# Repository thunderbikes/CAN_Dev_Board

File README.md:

# Alex CANBus DevBoard

## Repo:

https://github.com/alexm35644/CANBus_Devkit

## PCB:

[https://kicanvas.org/?github=https%3A%2F%2Fgithub.com%2Falexm35644%2FCANBus_Devkit%2Fblob%2Fmain%2FKiCAD_MCPtest%2FKiCAD_MCPtest.kicad_pro](https://kicanvas.org/?github=https%3A%2F%2Fgithub.com%2Falexm35644%2FCANBus_Devkit%2Fblob%2Fmain%2FKiCAD_MCPtest%2FKiCAD_MCPtest.kicad_pro)

# Summary

This project was made to develop CANBus for UBC ThunderBikes. It features 2 STM32 chips and 2 MCP2562FD CAN transceivers. 

# Firmware

## CAN_Firmware_Left

This firmware is for the chip on the left (near the USB Connector) and it acts as the “Master”. It sends CAN frames.

## CAN_firmware_Right

This firmware is meant for the chip on the right. It acts as the “Slave”. It receives the CAN frame and prints it via UART.

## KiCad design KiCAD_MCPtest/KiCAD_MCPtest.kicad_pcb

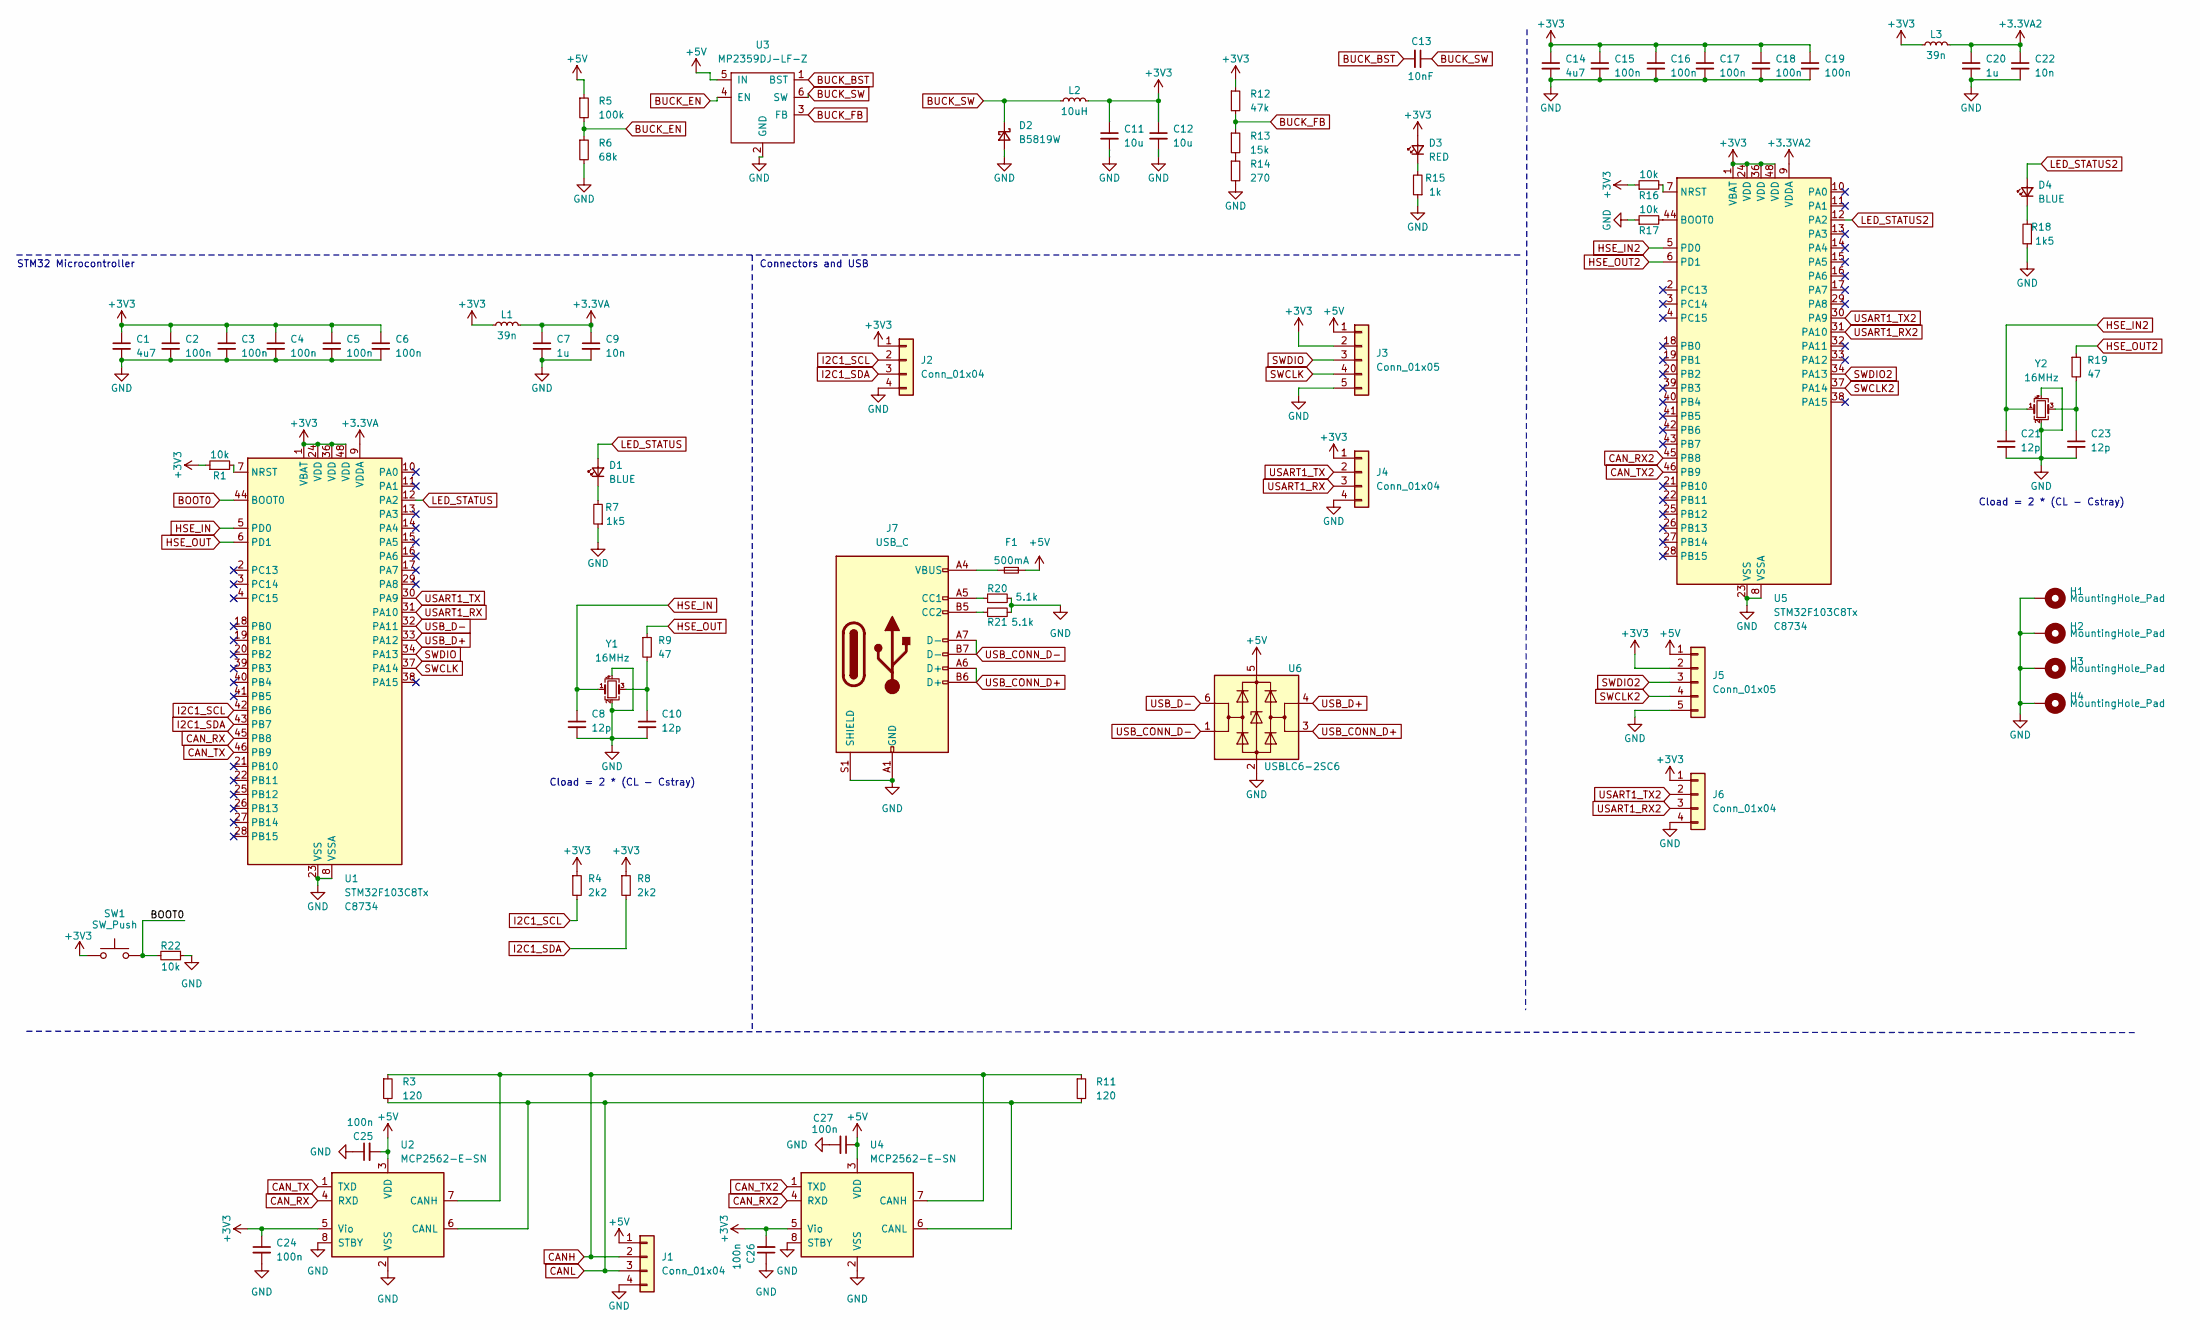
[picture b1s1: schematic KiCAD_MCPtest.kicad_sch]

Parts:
C1, C14: 4u7; C_0603_1608Metric; LCSC Part # C19666
C2, C3, C4, C5, C6, C15, C16, C17, C18, C19, C24, C25, C26, C27: 100n; C_0402_1005Metric; LCSC Part # C1525
C7, C20: 1u; C_0402_1005Metric; LCSC Part # C52923
C8, C10, C21, C23: 12p; C_0402_1005Metric; LCSC Part # C1547
C9, C22: 10n; C_0402_1005Metric; LCSC Part # C15195
C11, C12: 10u; C_1206_3216Metric; LCSC Part # C13585
C13: 10nF; C_0603_1608Metric; LCSC Part # C57112
D1, D4: BLUE; LED_0603_1608Metric; LCSC Part # C2286
D2: B5819W; D_SOD-123; LCSC Part # C64885
D3: RED; LED_0603_1608Metric; LCSC Part # C2286
F1: 500mA; Fuse_0603_1608Metric; LCSC Part # C210357
H1, H2, H3, H4: MountingHole_Pad; MountingHole_4.3mm_M4_Pad_Via
J1, J2, J4, J6: Conn_01x04; PinHeader_1x04_P2.54mm_Vertical
J3, J5: Conn_01x05; PinHeader_1x05_P2.54mm_Vertical
J7: USB_C; USB_C_HRO_TYPE-C-31-M-12; LCSC Part # C165948
L1, L3: 39n; L_0402_1005Metric; LCSC Part # C395063
L2: 10uH; L_Chilisin_BMRx00060630; LCSC Part # C128692
R1, R16, R17, R22: 10k; R_0402_1005Metric; LCSC Part # C25744
R3, R11: 120; R_0402_1005Metric; LCSC Part # C2909315
R4, R8: 2k2; R_0402_1005Metric; LCSC Part # C25879
R5: 100k; R_0603_1608Metric; LCSC Part # C25803
R6: 68k; R_0603_1608Metric; LCSC Part # C23231
R7, R18: 1k5; R_0603_1608Metric; LCSC Part # C22843
R9, R19: 47; R_0402_1005Metric; LCSC Part # C25118
R12: 47k; R_0603_1608Metric; LCSC Part # C25819
R13: 15k; R_0603_1608Metric; LCSC Part # C22809
R14: 270; R_0603_1608Metric; LCSC Part # C22966
R15: 1k; R_0603_1608Metric; LCSC Part # C21190
R20, R21: 5.1k; R_0402_1005Metric; LCSC Part # C25905
SW1: SW_Push; Button_TL3342; LCSC Part # C115351
U1, U5: STM32F103C8Tx; LQFP-48_7x7mm_P0.5mm; LCSC Part # C8734
U2, U4: MCP2562-E-SN; SOIC-8_3.9x4.9mm_P1.27mm; LCSC Part # C124016
U3: MP2359DJ-LF-Z; SOT-23-6; LCSC Part # C18198375
U6: USBLC6-2SC6; SOT-23-6; LCSC Part # C7519
Y1, Y2: 16MHz; Crystal_SMD_3225-4Pin_3.2x2.5mm; LCSC Part # C13738

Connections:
+3.3VA: C7.1, C9.1, L1.2, U1.9 (VDDA)
+3.3VA2: C20.1, C22.1, L3.2, U5.9 (VDDA)
+3V3: C1.1, C2.1, C3.1, C4.1, C5.1, C6.1, C11.1, C12.1, C14.1, C15.1, C16.1, C17.1, C18.1, C19.1, C24.1, C26.2, D3.2 (A), J2.1, J3.2, J4.1, J5.2, J6.1, L1.1, L2.2, L3.1, R1.1, R4.1, R8.1, R12.1, R16.1, SW1.1, U1.1 (VBAT), U1.24 (VDD), U1.36 (VDD), U1.48 (VDD), U2.5 (Vio), U4.5 (Vio), U5.1 (VBAT), U5.24 (VDD), U5.36 (VDD), U5.48 (VDD)
+5V: C25.2, C27.1, F1.2, J1.1, J3.1, J5.1, R5.1, U2.3 (VDD), U3.5 (IN), U4.3 (VDD), U6.5 (VBUS)
BOOT0: R22.2, SW1.2, U1.44 (BOOT0)
BUCK_BST: C13.2, U3.1 (BST)
BUCK_EN: R5.2, R6.1, U3.4 (EN)
BUCK_FB: R12.2, R13.1, U3.3 (FB)
BUCK_SW: C13.1, D2.1 (K), L2.1, U3.6 (SW)
CANH: J1.2, R3.1, R11.1, U2.7 (CANH), U4.7 (CANH)
CANL: J1.3, R3.2, R11.2, U2.6 (CANL), U4.6 (CANL)
CAN_RX: U1.45 (PB8), U2.4 (RXD)
CAN_RX2: U4.4 (RXD), U5.45 (PB8)
CAN_TX: U1.46 (PB9), U2.1 (TXD)
CAN_TX2: U4.1 (TXD), U5.46 (PB9)
GND: C1.2, C2.2, C3.2, C4.2, C5.2, C6.2, C7.2, C8.2, C9.2, C10.2, C11.2, C12.2, C14.2, C15.2, C16.2, C17.2, C18.2, C19.2, C20.2, C21.2, C22.2, C23.2, C24.2, C25.1, C26.1, C27.2, D2.2 (A), H1.1, H2.1, H3.1, H4.1, J1.4, J2.4, J3.5, J4.4, J5.5, J6.4, J7.A1 (GND), J7.A12 (GND), J7.B1 (GND), J7.B12 (GND), J7.S1 (SHIELD), R6.2, R7.1, R14.2, R15.1, R17.1, R18.1, R20.2, R21.2, R22.1, U1.8 (VSSA), U1.23 (VSS), U1.35 (VSS), U1.47 (VSS), U2.2 (VSS), U2.8 (STBY), U3.2 (GND), U4.2 (VSS), U4.8 (STBY), U5.8 (VSSA), U5.23 (VSS), U5.35 (VSS), U5.47 (VSS), U6.2 (GND), Y1.2, Y1.4, Y2.2, Y2.4
HSE_IN: C8.1, U1.5 (PD0), Y1.1
HSE_IN2: C21.1, U5.5 (PD0), Y2.1
HSE_OUT: R9.1, U1.6 (PD1)
HSE_OUT2: R19.1, U5.6 (PD1)
I2C1_SCL: J2.2, R4.2, U1.42 (PB6)
I2C1_SDA: J2.3, R8.2, U1.43 (PB7)
LED_STATUS: D1.2 (A), U1.12 (PA2)
LED_STATUS2: D4.2 (A), U5.12 (PA2)
unnamed: C10.1, R9.2, Y1.3
unnamed: C23.1, R19.2, Y2.3
unnamed: D1.1 (K), R7.2
unnamed: D3.1 (K), R15.2
unnamed: D4.1 (K), R18.2
unnamed: F1.1, J7.A4 (VBUS), J7.A9 (VBUS), J7.B4 (VBUS), J7.B9 (VBUS)
unnamed: J7.A5 (CC1), R20.1
unnamed: J7.B5 (CC2), R21.1
unnamed: R13.2, R14.1
unnamed: R1.2, U1.7 (NRST)
unnamed: R17.2, U5.44 (BOOT0)
unnamed: R16.2, U5.7 (NRST)
SWCLK: J3.4, U1.37 (PA14)
SWCLK2: J5.4, U5.37 (PA14)
SWDIO: J3.3, U1.34 (PA13)
SWDIO2: J5.3, U5.34 (PA13)
USART1_RX: J4.3, U1.31 (PA10)
USART1_RX2: J6.3, U5.31 (PA10)
USART1_TX: J4.2, U1.30 (PA9)
USART1_TX2: J6.2, U5.30 (PA9)
USB_CONN_D+: J7.A6 (D+), J7.B6 (D+), U6.3 (I/O2)
USB_CONN_D-: J7.A7 (D-), J7.B7 (D-), U6.1 (I/O1)
USB_D+: U1.33 (PA12), U6.4 (I/O2)
USB_D-: U1.32 (PA11), U6.6 (I/O1)

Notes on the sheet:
Cload = 2 * (CL - Cstray)
STM32 Microcontroller
Connectors and USB

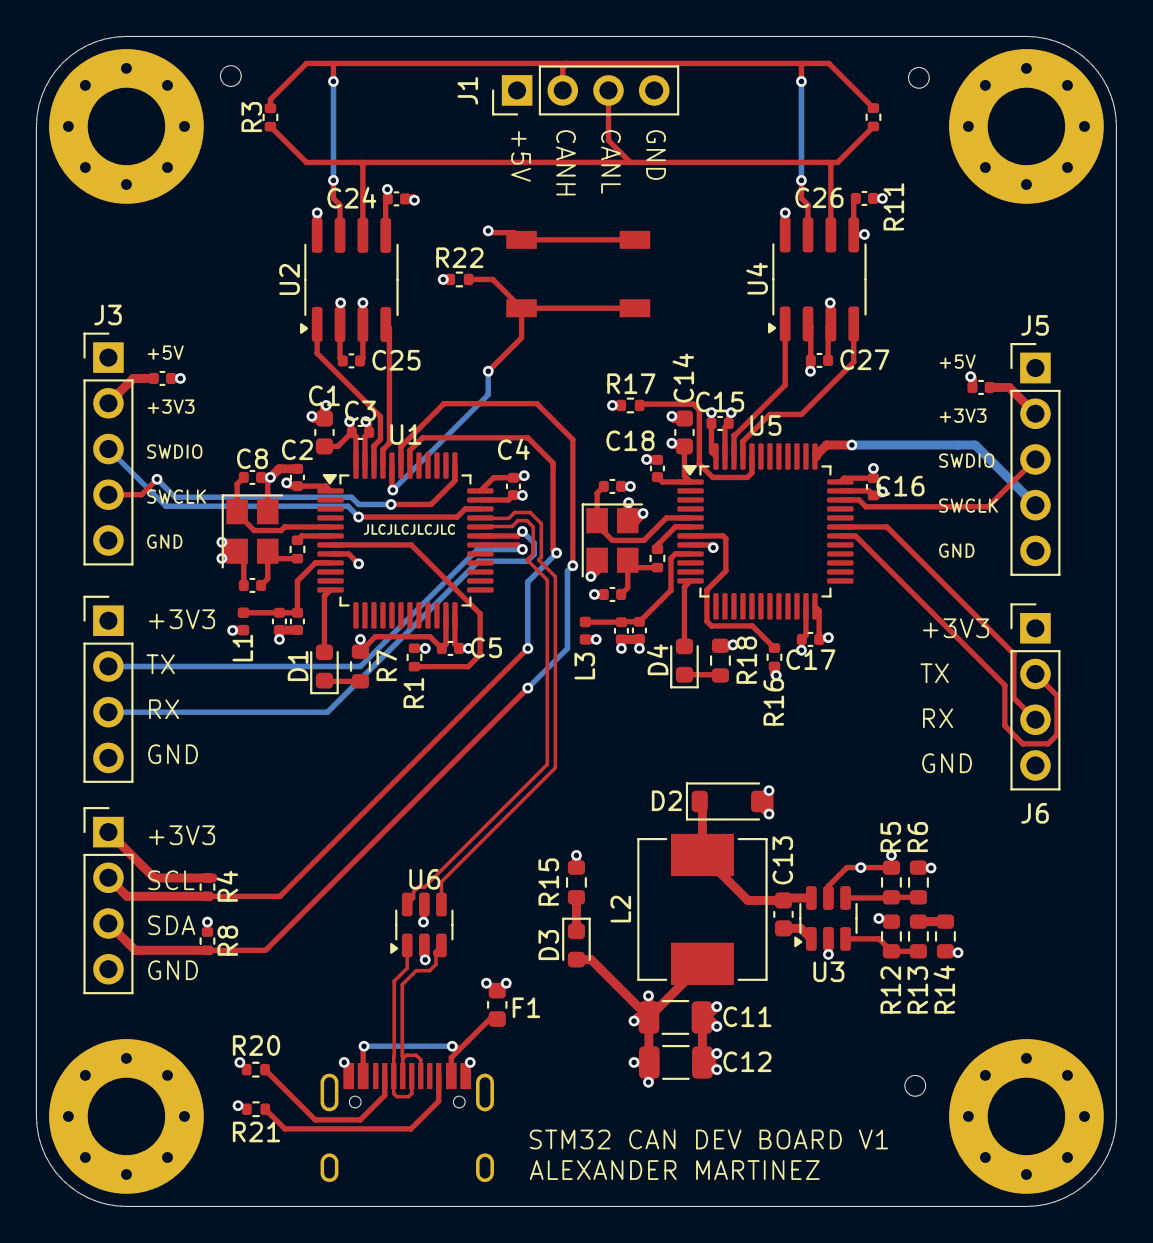
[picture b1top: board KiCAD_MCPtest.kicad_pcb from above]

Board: 4 copper layers, 60.0 x 65.0 mm, 75 parts (0 on the bottom side), 48 nets.

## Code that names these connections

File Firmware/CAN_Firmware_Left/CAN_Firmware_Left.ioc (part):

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Mcu.Name=STM32F103C(8-B)Tx
Mcu.Package=LQFP48
Mcu.UserName=STM32F103C8Tx
PA10.Mode=Asynchronous
PA10.Signal=USART1_RX
PA13.Mode=Serial_Wire
PA13.Signal=SYS_JTMS-SWDIO
PA14.Mode=Serial_Wire
PA14.Signal=SYS_JTCK-SWCLK
PA2.GPIOParameters=GPIO_Label
PA2.GPIO_Label=USER_LED
PA2.Signal=GPIO_Output
PA9.Mode=Asynchronous
PA9.Signal=USART1_TX
PB6.Mode=I2C
PB6.Signal=I2C1_SCL
PB7.Mode=I2C
PB7.Signal=I2C1_SDA
PB8.GPIOParameters=GPIO_PuPd
PB8.GPIO_PuPd=GPIO_PULLUP
PB8.Mode=CAN_Activate
PB8.Signal=CAN_RX
PB9.Mode=CAN_Activate
PB9.Signal=CAN_TX
PD0-OSC_IN.Mode=HSE-External-Oscillator
PD0-OSC_IN.Signal=RCC_OSC_IN
PD1-OSC_OUT.Mode=HSE-External-Oscillator
PD1-OSC_OUT.Signal=RCC_OSC_OUT
RCC.HSEDivPLL=RCC_HSE_PREDIV_DIV2
RCC.HSE_VALUE=16000000
RCC.SYSCLKFreq_VALUE=72000000
RCC.SYSCLKSource=RCC_SYSCLKSOURCE_PLLCLK
board=custom

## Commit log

2025-01-18 added .gitignore
2025-01-22 Update main.c
    Add Canbus erros messages
2025-01-23 Fixed LED
2025-01-25 Update main.c
    Can Error msg done
2025-01-25 Motor Controller CAN test
2025-01-25 toggling messages
2025-01-25 BMS messages
2025-01-27 uart testing
2025-02-02 trying
2025-02-02 UART RX working
2025-02-04 nothing
2025-02-07 USB testing
2025-02-27 bruh
2025-02-28 BMS Set func
2025-02-28 CAN send BMS Voltage
2025-02-28 Working with GUI
2025-02-28 Send and Receive Log
2025-03-15 working
